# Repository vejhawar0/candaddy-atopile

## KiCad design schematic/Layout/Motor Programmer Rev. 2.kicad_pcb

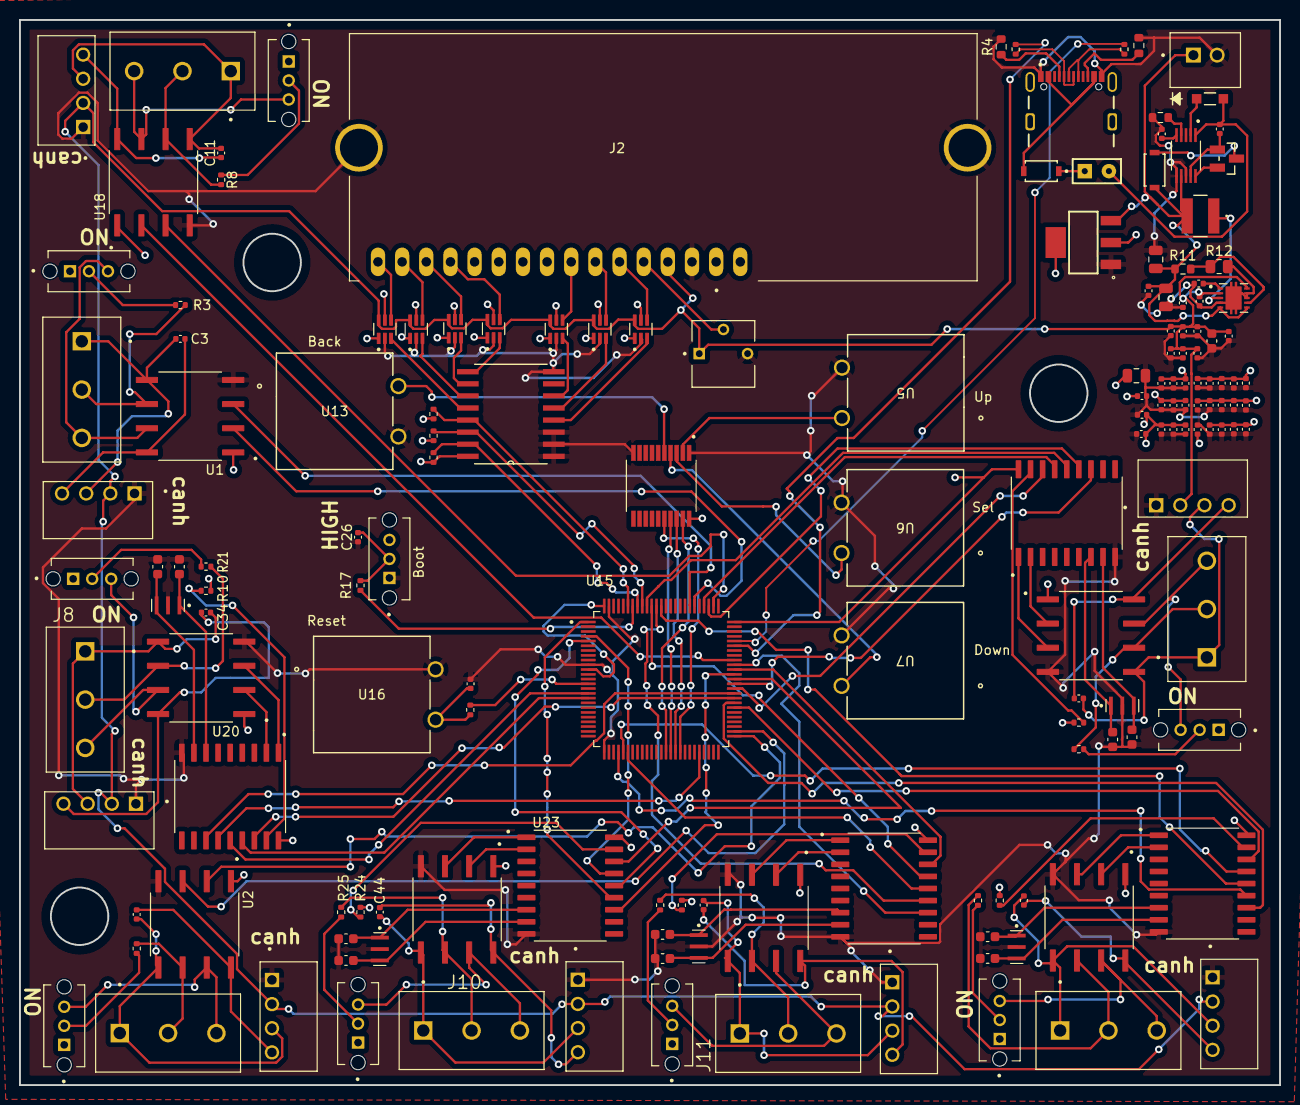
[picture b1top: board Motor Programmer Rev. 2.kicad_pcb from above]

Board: 2 copper layers, 132.5 x 112.0 mm, 160 parts (0 on the bottom side), 148 nets.

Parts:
C1, C3, C5, C6, C7, C8, C9, C10, C11, C12, C14, C15, C16, C17, C18, C21, C22, C23, C25, C26, C27, C28, C29, C33, C34, C35, C38, C39, C40, C43, C44, C45, C48, C49, C50, C51, C52, C53, C54, C55, C56, C57, C58, C59, C60, C61, C62, C63, C64: 100nF; C_0402_1005Metric
C2, C19, C24: 10uF; C_0805_2012Metric
C4: 0.1uF; C_0402_1005Metric
C13, C30, C31, C32, C36, C37, C41, C42, C46, C47: 7pF; C_0603_1608Metric
C20: 22uF; C_0603_1608Metric
CR1, CR2: SMD110PL-TP; SOD-123FL_MCC
J1: USB4105-GF-A; GCT_USB4105-GF-A
J2: LCM-S01602DTR_M; LCD_LCM-S01602DTR_M
J3, J5, J6, J7, J8, J9, J10, J11: TB006-508-03BE; CUI_TB006-508-03BE
J4: B2B-XH-A; JST_B2B-XH-A
J12: TS-102-G-A; SAMTEC_TS-102-G-A
L1: 3.3uH; IND_TAIYO_NRS4018_TAY
LED1: IR12-21C/TR8; LED_IR12-21C&slash_TR8_EVE
PS1, PS2, PS3, PS4, PS5, PS6, PS7, PS8: RFM-0505S; CONV_RFM-0505S
Q1: DMP3099L-7; DMP3099L-7_DIO
R1, R2: 22; R_0402_1005Metric
R3, R6, R7, R8, R21, R23, R25, R27: 120; R_0402_1005Metric
R4, R5, R13: 5.1k; R_0603_1608Metric
R9, R10, R17, R22, R24, R26: 10k; R_0402_1005Metric
R11: 2.26M; R_0603_1608Metric
R12: 250k; R_0805_2012Metric
R16: 100; R_0402_1005Metric
R18, R19, R20: 4.7k; R_0402_1005Metric
S1, S2, S3, S4, S5, S6, S7, S8, S9: OS102011MS2QN1; SW_OS102011MS2QN1
U1, U2, U4, U18, U20, U22, U24, U26: ISO1050DUBR; SOP254P1040X485-8N
U3: LD1117S33TR; SOT230P700X180-4N
U5, U6, U7, U13, U16: GPTS203211B; SWITCH_03211B
U8: MAX6818EAP_T; SOP65P777X199-20N
U9: PCF8574T_3_518; SOIC127P1032X265-16N
U12: TPS61202DRCT; VREG_V62_16624-01YE
U14: MAX1898EUB42_T; SOP50P490X110-10N
U15: STM32F767VGT6; QFP50P1600X1600X160-100N
U17, U19, U21, U23, U25: MCP2515-I_SO; SOIC127P1030X265-18N
U27, U28, U29, U30, U31, U32, U33: 74LVC1T45GW_125; SOP65P210X110-6N
VR1: 3362P-1-103LF; TRIM_3362P-1-103LF
Y1, Y2, Y3, Y4, Y5: CSTNE16M0V530000R0; OSC_CSTNE16M0V530000R0

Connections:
+3.3V: C2.2, C4.1, C5.1, C7.1, C9.1, C10.2, C12.1, C14.2, C16.2, C18.2, C27.1, C28.1, C29.1, C33.2, C35.1, C38.2, C40.1, C43.2, C45.1, C48.2, C50.1, C51.2, C54.2, C56.2, C58.2, C60.2, C62.2, C64.2, R9.1, R10.1, R18.1, R19.1, R20.1, R22.1, R24.1, R26.1, S3.3, U1.1 (VCC1), U2.1 (VCC1), U3.2 (OUT), U3.4 (OUT__1), U4.1 (VCC1), U8.20 (VCC), U9.16 (VDD), U15.11 (VDD), U15.75 (VDD), U15.100 (VDD), U17.18 (VDD), U18.1 (VCC1), U19.18 (VDD), U20.1 (VCC1), U21.18 (VDD), U22.1 (VCC1), U23.18 (VDD), U24.1 (VCC1), U25.18 (VDD), U26.1 (VCC1), U27.1 (VCC(A)), U27.5 (DIR), U28.1 (VCC(A)), U28.5 (DIR), U29.1 (VCC(A)), U29.5 (DIR), U30.1 (VCC(A)), U30.5 (DIR), U31.1 (VCC(A)), U31.5 (DIR), U32.1 (VCC(A)), U32.5 (DIR), U33.1 (VCC(A)), U33.5 (DIR)
+5V: C15.2, C17.2, C20.1, C52.2, C53.2, C55.2, C57.2, C59.2, C61.2, C63.2, J2.2 (VDD), PS1.2 (+VIN), PS2.2 (+VIN), PS3.2 (+VIN), PS4.2 (+VIN), PS5.2 (+VIN), PS6.2 (+VIN), PS7.2 (+VIN), PS8.2 (+VIN), U12.2 (VOUT), U12.10 (FB), U27.6 (VCC(B)), U28.6 (VCC(B)), U29.6 (VCC(B)), U30.6 (VCC(B)), U31.6 (VCC(B)), U32.6 (VCC(B)), U33.6 (VCC(B)), VR1.1
/CAN1/CANH: J3.3, S1.3, U1.7 (CANH)
/CAN1/CANL: J3.2, R3.2, U1.6 (CANL)
/CAN1/CAN_GND: C3.2, J3.1, PS1.3 (-VOUT), U1.5 (GND2)
/CAN1/CAN_VDD: C3.1, PS1.4 (+VOUT), U1.8 (VCC2)
/CAN1_RX: U1.2 (RXD), U15.81 (PD0)
/CAN1_TX: U1.3 (TXD), U15.82 (PD1)
/CAN2/CANH: J5.3, S2.3, U2.7 (CANH)
/CAN2/CANL: J5.2, R6.2, U2.6 (CANL)
/CAN2/CAN_GND: C6.2, J5.1, PS2.3 (-VOUT), U2.5 (GND2)
/CAN2/CAN_VDD: C6.1, PS2.4 (+VOUT), U2.8 (VCC2)
/CAN2_RX: U2.2 (RXD), U15.51 (PB12)
/CAN2_TX: U2.3 (TXD), U15.52 (PB13)
/CAN3/CANH: J7.3, S5.3, U18.7 (CANH)
/CAN3/CANL: J7.2, R8.2, U18.6 (CANL)
/CAN3/CAN_GND: C11.2, J7.1, PS4.3 (-VOUT), U18.5 (GND2)
/CAN3/CAN_VDD: C11.1, PS4.4 (+VOUT), U18.8 (VCC2)
/CAN3_RX: U15.67 (PA8), U18.2 (RXD)
/CAN3_TX: U15.77 (PA15), U18.3 (TXD)
/CAN4/CANH: J6.3, S4.3, U4.7 (CANH)
/CAN4/CANL: J6.2, R7.2, U4.6 (CANL)
/CAN4/CAN_GND: C8.2, J6.1, PS3.3 (-VOUT), U4.5 (GND2)
/CAN4/CAN_RX: U4.2 (RXD), U17.2 (RXCAN)
/CAN4/CAN_TX: U4.3 (TXD), U17.1 (TXCAN)
/CAN4/CAN_VDD: C8.1, PS3.4 (+VOUT), U4.8 (VCC2)
/CAN4/OSC1: C13.1, U17.8 (OSC1), Y1.3
/CAN4/OSC2: C30.1, U17.7 (OSC2), Y1.1
/CAN5/CANH: J8.3, S6.3, U20.7 (CANH)
/CAN5/CANL: J8.2, R21.2, U20.6 (CANL)
/CAN5/CAN_GND: C34.2, J8.1, PS5.3 (-VOUT), U20.5 (GND2)
/CAN5/CAN_RX: U19.2 (RXCAN), U20.2 (RXD)
/CAN5/CAN_TX: U19.1 (TXCAN), U20.3 (TXD)
/CAN5/CAN_VDD: C34.1, PS5.4 (+VOUT), U20.8 (VCC2)
/CAN5/OSC1: C32.1, U19.8 (OSC1), Y2.3
/CAN5/OSC2: C31.1, U19.7 (OSC2), Y2.1
/CAN6/CANH: J9.3, S7.3, U22.7 (CANH)
/CAN6/CANL: J9.2, R23.2, U22.6 (CANL)
/CAN6/CAN_GND: C39.2, J9.1, PS6.3 (-VOUT), U22.5 (GND2)
/CAN6/CAN_RX: U21.2 (RXCAN), U22.2 (RXD)
/CAN6/CAN_TX: U21.1 (TXCAN), U22.3 (TXD)
/CAN6/CAN_VDD: C39.1, PS6.4 (+VOUT), U22.8 (VCC2)
/CAN6/OSC1: C37.1, U21.8 (OSC1), Y3.3
/CAN6/OSC2: C36.1, U21.7 (OSC2), Y3.1
/CAN7/CANH: J10.3, S8.3, U24.7 (CANH)
/CAN7/CANL: J10.2, R25.2, U24.6 (CANL)
/CAN7/CAN_GND: C44.2, J10.1, PS7.3 (-VOUT), U24.5 (GND2)
/CAN7/CAN_RX: U23.2 (RXCAN), U24.2 (RXD)
/CAN7/CAN_TX: U23.1 (TXCAN), U24.3 (TXD)
/CAN7/CAN_VDD: C44.1, PS7.4 (+VOUT), U24.8 (VCC2)
/CAN7/OSC1: C42.1, U23.8 (OSC1), Y4.3
/CAN7/OSC2: C41.1, U23.7 (OSC2), Y4.1
/CAN8/CANH: J11.3, S9.3, U26.7 (CANH)
/CAN8/CANL: J11.2, R27.2, U26.6 (CANL)
/CAN8/CAN_GND: C49.2, J11.1, PS8.3 (-VOUT), U26.5 (GND2)
/CAN8/CAN_RX: U25.2 (RXCAN), U26.2 (RXD)
/CAN8/CAN_TX: U25.1 (TXCAN), U26.3 (TXD)
/CAN8/CAN_VDD: C49.1, PS8.4 (+VOUT), U26.8 (VCC2)
/CAN8/OSC1: C47.1, U25.8 (OSC1), Y5.3
/CAN8/OSC2: C46.1, U25.7 (OSC2), Y5.1
/CS1: U15.57 (PD10), U17.16 (~CS)
/CS2: U15.59 (PD12), U19.16 (~CS)
/CS3: U15.61 (PD14), U21.16 (~CS)
/CS4: U15.63 (PC6), U23.16 (~CS)
/CS6: U15.65 (PC8), U25.16 (~CS)
/D+: R1.1, U15.71 (PA12)
/D-: R2.1, U15.70 (PA11)
/Deb_back: U8.16 (OUT4), U15.42 (PE12)
/Deb_left: U8.19 (OUT1), U15.39 (PE9)
/Deb_right: U8.17 (OUT3), U15.40 (PE10)
/Deb_select: U8.18 (OUT2), U15.41 (PE11)
/INT1: U15.58 (PD11), U17.12 (~INT)
/INT2: U15.60 (PD13), U19.12 (~INT)
/INT3: U15.62 (PD15), U21.12 (~INT)
/INT4: U15.64 (PC7), U23.12 (~INT)
/INT6: U15.66 (PC9), U25.12 (~INT)
/LCD_Int: R20.2, U9.13 (~INT), U15.95 (PB8)
/LED/D4H: J2.11 (DB4), U31.4 (B)
/LED/D4L: U9.9 (P4), U31.3 (A)
/LED/D5H: J2.12 (DB5), U32.4 (B)
/LED/D5L: U9.10 (P5), U32.3 (A)
/LED/D6H: J2.13 (DB6), U30.4 (B)
/LED/D6L: U9.11 (P6), U30.3 (A)
/LED/D7H: J2.14 (DB7), U33.4 (B)
/LED/D7L: U9.12 (P7), U33.3 (A)
/LED/E_H: J2.6 (E), U29.4 (B)
/LED/E_L: U9.6 (P2), U29.3 (A)
/LED/RS_H: J2.4 (RS), U27.4 (B)
/LED/RS_L: U9.4 (P0), U27.3 (A)
/LED/RW_H: J2.5 (R/~W), U28.4 (B)
/LED/RW_L: U9.5 (P1), U28.3 (A)
/SCL: R18.2, U9.14 (SCL), U15.92 (PB6)
/SDA: R19.2, U9.15 (SDA), U15.93 (PB7)
/SPI1_MISO: U15.30 (PA6), U17.15 (SO)
/SPI1_MOSI: U15.88 (PD7), U17.14 (SI)
/SPI1_SCK: U15.29 (PA5), U17.13 (SCK)
/SPI2_MISO: U15.17 (PC2), U19.15 (SO)
/SPI2_MOSI: U15.16 (PC1), U19.14 (SI)
/SPI2_SCK: U15.46 (PB10), U19.13 (SCK)
/SPI3_MISO: U15.79 (PC11), U21.15 (SO)
/SPI3_MOSI: U15.91 (PB5), U21.14 (SI)
/SPI3_SCK: U15.78 (PC10), U21.13 (SCK)
/SPI4_MISO: U15.4 (PE5), U23.15 (SO)
/SPI4_MOSI: U15.5 (PE6), U23.14 (SI)
/SPI4_SCK: U15.1 (PE2), U23.13 (SCK)
/SPI6_MISO: U15.90 (PB4), U25.15 (SO)
/SPI6_MOSI: U15.31 (PA7), U25.14 (SI)
/SPI6_SCK: U15.89 (PB3), U25.13 (SCK)
/USB + Power Source/CS: Q1.2, U14.10 (CS)
/USB + Power Source/DRV: C22.2, Q1.1, U14.9 (DRV)
/USB + Power Source/USB_D+: J1.A6 (DP1), J1.B6 (DP2), R1.2
/USB + Power Source/USB_D-: J1.A7 (DN1), J1.B7 (DN2), R2.2
/USB + Power Source/USB_VBUS: CR2.2, J1.A4-B9 (VBUS), J1.B4-A9 (VBUS)
/USB + Power Source/UVLO: R11.2, R12.1, U12.7 (UVLO)
GND: C1.2, C2.1, C4.2, C5.2, C7.2, C9.2, C10.1, C12.2, C13.2, C14.1, C15.1, C16.1, C17.1, C18.1, C19.2, C20.2, C21.2, C23.2, C24.2, C25.2, C26.1, C27.2, C28.2, C29.2, C30.2, C31.2, C32.2, C33.1, C35.2, C36.2, C37.2, C38.1, C40.2, C41.2, C42.2, C43.1, C45.2, C46.2, C47.2, C48.1, C50.2, C51.1, C52.1, C53.1, C54.1, C55.1, C56.1, C57.1, C58.1, C59.1, C60.1, C61.1, C62.1, C63.1, C64.1, J1.A1-B12 (GND), J1.B1-A12 (GND), J2.1 (VSS), J2.S1 (SHIELD), J2.S2 (SHIELD__1), J4.2, PS1.1 (-VIN), PS2.1 (-VIN), PS3.1 (-VIN), PS4.1 (-VIN), PS5.1 (-VIN), PS6.1 (-VIN), PS7.1 (-VIN), PS8.1 (-VIN), R4.2, R5.1, R12.2, R13.2, S3.1, U1.4 (GND1), U2.4 (GND1), U3.1 (GND), U4.4 (GND1), U5.6, U6.6, U7.6, U8.1 (EN), U8.10 (GND), U9.1 (A0), U9.2 (A1), U9.3 (A2), U9.8 (VSS), U12.4 (PGND), U12.8 (PS), U12.9 (GND), U12.11 (EP), U13.6, U14.6 (RSTRT), U14.8 (GND), U15.10 (VSS), U15.26 (VSS), U15.99 (VSS), U16.1, U17.9 (VSS), U18.4 (GND1), U19.9 (VSS), U20.4 (GND1), U21.9 (VSS), U22.4 (GND1), U23.9 (VSS), U24.4 (GND1), U25.9 (VSS), U26.4 (GND1), U27.2 (GND), U28.2 (GND), U29.2 (GND), U30.2 (GND), U31.2 (GND), U32.2 (GND), U33.2 (GND), VR1.3, Y1.2, Y2.2, Y3.2, Y4.2, Y5.2
unnamed: C25.1, R16.1, U16.6
unnamed: C26.2, R17.1, S3.2
unnamed: CR1.2, Q1.3
unnamed: CR2.1, J12.01
unnamed: J1.A5 (CC1), R4.1
unnamed: J1.B5 (CC2), R5.2
unnamed: J2.3 (VO), VR1.2
unnamed: R3.1, S1.2
unnamed: R6.1, S2.2
unnamed: R7.1, S4.2
unnamed: R8.1, S5.2
unnamed: R21.1, S6.2
unnamed: R23.1, S7.2
unnamed: R25.1, S8.2
unnamed: R27.1, S9.2
unnamed: U5.1, U8.2 (IN1)
unnamed: U6.1, U8.3 (IN2)
unnamed: U7.1, U8.4 (IN3)
unnamed: U8.5 (IN4), U13.1
unnamed: L1.1, U12.3 (L)
unnamed: C21.1, U12.1 (VAUX)
unnamed: C23.1, U14.5 (CT)
unnamed: R13.1, U14.4 (ISET)
unnamed: LED1.1, U14.2 (~CHG)
unnamed: R16.2, U15.14 (NRST)
unnamed: R17.2, U15.94 (PF11-BOOT0)
unnamed: R9.2, U17.17 (~RESET)
unnamed: R10.2, U19.17 (~RESET)
unnamed: R22.2, U21.17 (~RESET)
unnamed: R24.2, U23.17 (~RESET)
unnamed: R26.2, U25.17 (~RESET)
VCC: C1.1, C19.1, C24.1, CR1.1, J4.1, L1.2, R11.1, U3.3 (IN), U12.5 (VIN), U12.6 (EN), U14.7 (BATT)
VDD: C22.1, J12.02, LED1.2, U14.1 (IN)

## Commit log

2024-05-15 schematic
2024-05-16 Added compatibility for 8 CAN devices and updated necessary parts and schematics for viewing. Will continue to work on battery support.
2024-05-24 First revision of the Motor Flasher
2024-05-24 Slight revision made for Schematic view
2024-06-05 Atopile Build
2024-06-05 moving files to top level
2024-06-05 Second build
2024-06-05 Third build
2024-06-22 Adding in revisions 2 and 3
